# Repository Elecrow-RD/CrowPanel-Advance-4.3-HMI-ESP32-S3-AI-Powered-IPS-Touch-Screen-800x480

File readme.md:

## Menu
### 1, Product picture
### 2, Product version number
### 3, product information
### 4, Use the driver module
### 5,Quick Start
### 6,Folder structure.
### 7,Pin definition
### 8,Guidelines for downloading some of the files from the github repository

### 1, Product picture

### 2, Product version number

|      | Hardware | Software | Remark |
| ---- | -------- | -------- | ------ |
| 1    | V1.0     | V1.0     | old |
| 2    | V1.1     | V1.1     | old |
| 3    | V1.2     | V1.2     | old |
| 4    | V1.3     | V1.2     | latest |

### Version update points:
① Version 1.1 updated the control of backlight on the basis of the original, the backlight of version 1.2 is controlled by STC8H1K28 microcontroller, and the backlight is lit in the program by sending the value to this microcontroller address (0x30). The values are 0-245, where 245 switches off the backlight and 0 is the maximum brightness.

② Version 1.1 has a new option for function switching, see above for details. When using the case, please select the corresponding program to test or modify according to the version number of your motherboard.

## Version 1.2
Only the button component has been updated. All other hardware and I/O pins remain the same as in the previous version.

## Version 1.3
Version 1.3 is simply an update to the previous version that modifies the packaging of the touchscreen FPC connector. There are no other differences.

### 3, product information

| Main Chip-ESP32-S3-WROOM-1-N16R8         |                                                              |
| -------------------------------------------- | ------------------------------------------------------------ |
| CPU/SoC                                      | high-performance Xtensa 32-bit LX7 dual-core processor, with up to 240MHz |
| System Memory                                | 512KB SRAM、8M PSRAM                                         |
| Memory                                       | 16M Flash，384KB ROM                                         |
| Development Language                         | MicroPython、C/C++                                           |
| Development Environment                      | ESP-IDF、Arduino IDE、PlatformIO、MicroPython         |
| **Screen**                                   |                                                              |
| Size                                         | 4.3 inch                                                     |
| Diver IC                                     | ST7265                                                       |
| Resolution                                   | 800*480                                                      |
| Display Panel                                | IPS Panel                                                    |
| Touch Panel                                  | Capacitive Single Touch                                      |
| Viewing Angle                                | 178°                                                         |
| Brightness                                   | 400 cd/m²(Typ.)                                              |
| Color Depth                                  | 16-bit                                                       |
| **Wireless Communication - Onboard Antenna** |                                                              |
| WiFi                                         | Support 2.4GHz, 802.11a/b/g/n                                |
| Bluetooth                                    | Support Bluetooth 5.0 and BLE                                |
| Other                                        | **LoRa**                                                     |
| **Interface/Function**                       |                                                              |
| Interface                                    | USB port, UART, I2C, SD card slot, battery socket, speaker port, microphone, etc. |
| Function                                     | RTC clock, audio amplifier, volume control, battery charge management, USB to UART, etc. |
| **Button/LED Indicator**                     |                                                              |
| Reset Button                                 | Yes, press to reset the device                               |
| Boot Button                                  | Yes, press and hold the power button to burn the program     |
| PWR                                          | Power indicator                                              |
| CHG                                          | Lithium battery charging status, completion indication       |
| **Other**                                    |                                                              |
| Installation method                          | Back hanging, fixed hole                                     |
| Operating temperature                        | -20~70 °C                                                    |
| Storage temperature                          | -30~80 °C                                                    |
| Power Input                                  | 5V/2A, USB or UART terminal                                  |
| Active Area                                  | 95.5mm*54mm                                                  |
| Dimensions                                   | 121.9*75.6*15.3mm                                            |

### 4, Use the driver module

| Name   | dependency library                      |
| ------ | --------------------------------------- |
| LVGL   | lvgl/lvgl@8.3.3                         |
| ST7789 | Adafruit GFX Library<br/>version=1.11.0 |

### 5,Quick Start
### Arduino IDE starts

#### Teaching Case Path：./example/example_code4.3

1.Download the library files used by this product to the 'libraries' folder.

C:\Users\Documents\Arduino\libraries\

2.Open the Arduino IDE

3.Open the code configuration environment and burn it

### ESP-IDF starts

#### Teaching Case Path：./example/idf_code

1.Right-click on an empty space in the project folder and select "Open with VS Code" to open the project.

2.In the IDF plug-in, select the port, then compile and flash

### 6,Folder structure.
|--3D file： Contains 3D model files (.stp) for the hardware. These files can be used for visualization, enclosure design, or integration into CAD software.

|--Datasheet: Includes datasheets for components used in the project, providing detailed specifications, electrical characteristics, and pin configurations.

|--Eagle_SCH&PCB: Contains Eagle CAD schematic (.sch) and PCB layout (.brd) files. These are used for circuit design and PCB manufacturing.

|--example: Provides example code and projects to demonstrate how to use the hardware and libraries. These examples help users get started quickly.

|--factory_firmware: Stores pre-compiled factory firmware that can be directly flashed onto the device. This ensures the device runs the default functionality.

|--factory_sourcecode: Contains the source code for the factory firmware, allowing users to modify and rebuild the firmware as needed.

|--libraries: Includes necessary libraries required for compiling and running the project. These libraries provide drivers and additional functionalities for the hardware.

|--Squareline_studio Instructions for use: Squareline_studio instructions: Demonstrate the use of squareline studio.

### 7,Pin definition

#define HSPI_MISO  4

#define HSPI_MOSI  6

#define HSPI_SCLK  5

#define HSPI_SS    19

#define SD_MOSI 6

#define SD_MISO 4

#define SD_SCK 5

#define SD_CS 0 //The chip selector pin is not connected to IO

#define I2S_DOUT 4

#define I2S_BCLK 5

#define I2S_LRC 6

​      cfg.pin_d0 = GPIO_NUM_21;    // B0

​      cfg.pin_d1 = GPIO_NUM_47;    // B1

​      cfg.pin_d2 = GPIO_NUM_48;   // B2

​      cfg.pin_d3 = GPIO_NUM_45;    // B3

​      cfg.pin_d4 = GPIO_NUM_38;    // B4

​      cfg.pin_d5 = GPIO_NUM_9;    // G0

​      cfg.pin_d6 = GPIO_NUM_10;    // G1

​      cfg.pin_d7 = GPIO_NUM_11;    // G2

​      cfg.pin_d8 = GPIO_NUM_12;   // G3

​      cfg.pin_d9 = GPIO_NUM_13;   // G4

​      cfg.pin_d10 = GPIO_NUM_14;   // G5

​      cfg.pin_d11 = GPIO_NUM_7;  // R0

​      cfg.pin_d12 = GPIO_NUM_17;  // R1

​      cfg.pin_d13 = GPIO_NUM_18;  // R2

​      cfg.pin_d14 = GPIO_NUM_3;  // R3

​      cfg.pin_d15 = GPIO_NUM_46;  // R4

      cfg.pin_henable = GPIO_NUM_42;
      
      cfg.pin_vsync = GPIO_NUM_41;
      
      cfg.pin_hsync = GPIO_NUM_40;
      
      cfg.pin_pclk = GPIO_NUM_39;

#define TOUCH_GT911_SCL 16

#define TOUCH_GT911_SDA 15

### 8,Guidelines for downloading some of the files from the github repository

##### 1, open the link in your browser: https://downgit.github.io/

##### 2, paste the URL of the GitHub destination folder in the input box (example format: `https://github.com/username/repository name/tree/branch name/folder path`)

##### 3, even a that way to download the file.

①Click the “Create Download Link” button to create a download link, copy the link and open it with your browser to download the contents of the corresponding folder directly.

②Click Download, and you can also download it directly.

#### Note: DownGit downloads are stored by default in **your browser's default downloads folder**, usually:

- **Windows**: `C:\Users\your username\Downloads\` (downloads folder)
- **macOS**: `~/Downloads/` (downloads folder)
- **Linux**: `~/Downloads/` (Downloads folder)

If you change the default download path in your browser, the file will be stored in the download location you set. You can find the downloaded file path in your browser's **Download History** (shortcut `Ctrl + J` or `Cmd + J`).

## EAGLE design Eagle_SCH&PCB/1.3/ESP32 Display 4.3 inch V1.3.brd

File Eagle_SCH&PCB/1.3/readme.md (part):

# 4.3-inch CrowPanel Advance HMI Product Hardware Driver Guide

| Item | Details |
|---|---|
| Document Version | V1.0 |
| Date | 2026-07-30 |
| Author | Codex (compiled from the project schematics and verified example code) |
| Applicable Hardware | ESP32 Display 4.3 inch V1.3 / ESP32-S3-N16R8 |
| Schematic Baseline | `1.3/ESP32 Display 4.3 inch V1.3.sch`, `1.3/ESP32-Display-4.3-inch-V1.3.pdf` |
| Software Baseline | Arduino-ESP32 3.3.8; LovyanGFX 1.2.25; LVGL 9.1.0 |

> **Authority rule:** This document uses the actual configurations from successfully tested examples in the repository as the driver baseline and verifies electrical connections against the Eagle V1.3 schematic netlist. If the two conflict, the code values take precedence, and the discrepancy is recorded under “Differences and Risks.” Capabilities without supporting code evidence are marked as “schematic-confirmed/requires hardware verification” and must not be considered verified.

## 1. Summary of Conclusions

- The main controller is an ESP32-S3-WROOM-1-N16R8 (16 MB Flash, 8 MB PSRAM), and the Arduino examples use ESP32 core 3.3.8.
- The display has an 800×480 resolution, RGB565 pixel format, and a 16-bit parallel RGB interface. The stable code baseline uses a 16 MHz pixel clock; the repository also contains examples using 18 MHz and 21 MHz.
- According to the code, the touch controller is a GT911 with I2C address `0x5D`, SDA/SCL on GPIO15/GPIO16, and a 400 kHz bus speed. The code uses polling rather than interrupts.
- According to the code, the onboard STC8 auxiliary MCU uses I2C address `0x30` and handles board-level control of the backlight, touch recovery, speaker, and other functions. Its firmware protocol is not included; only a few verified commands are available.
- GPIO4/5/6 and GPIO19/20 are multiplexed through CH486F devices and DIP switches. SD, I2S audio, wireless SPI, digital microphone, and UART/Zigbee cannot all be enabled simultaneously without restrictions.
- DHT20, nRF24L01, SX1262, and Zigbee are external example devices connected through expansion ports; they are not onboard devices in the V1.3 schematic.

## 2. Evidence Levels and Porting Principles

| Level | Definition | Usage Principle |
|---|---|---|
| A - Code-verified | A complete initialization and execution path exists in the repository's product examples | Preferred values for porting |
| B - Schematic-confirmed | Explicitly present in the V1.3 schematic but not directly driven by the ESP32 examples | May be used for development, but hardware testing must be added |
| C - External example | Example code has been run with the device connected externally through an expansion port | Valid only when the corresponding module is connected and the DIP switches are set to the appropriate mode |
| D - Inferred | Inferred from device functionality or net relationships, without protocol documentation or actual testing | Must not be presented as a production-ready capability |

When porting, select a GPIO multiplexing scenario before initializing peripherals. Do not simply combine all examples. The display and I2C bus may be treated as persistent infrastructure; functions associated with GPIO4/5/6 and GPIO19/20 must be enabled mutually exclusively according to the product scenario.

## 3. Peripheral Overview

| Category | Device/Interface | Connection and Driver | Status |
|---|---|---|---|
| Main controller | ESP32-S3-WROOM-1-N16R8 | Arduino HAL; Wi-Fi; GPIO Matrix; PSRAM | A |
| Display | 4.3-inch 800×480 IPS | 16-bit RGB565, GPIO3/7/9-14/17/18/21/38/45-48, PCLK 39, DE 42, HSYNC 40, VSYNC 41 | A |
| Touch | GT911 (identified by code) | I2C0, SDA 15, SCL 16, `0x5D`, 400 kHz, polling | A |
| Board-control MCU | STC8H1K28 | Shares I2C 15/16 with the ESP32; accessed at `0x30` by the code | A (incomplete protocol) |
| RTC | PCF8563-compatible device + CR1220 | I2C 15/16, 32.768 kHz crystal | B |
| Storage | MicroSD card socket | SPI: MOSI 6, MISO 4, SCK 5; CS not connected to the main controller | A |
| Audio output | NS4168 + right-channel connector | I2S: DOUT 4, BCLK 5, LRCLK 6; board-control command 248 enables the speaker | A |
| Audio input | LMD3526B261 digital microphone | CLK 19, DATA 20; I2S/PDM characteristics require additional testing against the device documentation | B |
| Wireless expansion | J9/J11/J12 | SPI 4/5/6; control pins 8/19/20/2; 3.3 V/optional 5 V | A/C |
| nRF24L01 | External module | SPI 4/5/6, CSN 19, CE 20 | C |
| SX1262 LoRa | External module | SPI 4/5/6, NSS 8, DIO1 20, RESET 19, BUSY 2 | C |
| Zigbee/UART | External module | UART1 RX 19, TX 20, 115200 8N1 | C |
| Temperature and humidity | External DHT20 | I2C 15/16, address `0x38` | C |
| USB-UART | CH340K + automatic download circuit | USB-C D+/D-; connected to ESP32 UART0, EN, and IO0 | B (programming path implicitly used) |
| Expansion interfaces | J2/J10/J13/J14 | UART0, STC UART, I2C, power | B |
| Power management | TP4059, RY3420, MT9201, MOSFET power gating | USB/external 5 V/Li-ion battery input; 3.3 V and backlight boost | B |
| Actuator | Passive buzzer B2 | Driven by STC P2.7 through an NPN transistor | B |
| Indicators/keys | BOOT, RESET, charging/power LEDs, K1 DIP switch | IO0, EN; status LEDs managed by the STC; K1 selects multiplexed channels | B |

## 4. Authoritative GPIO Assignment Table

| ESP32 GPIO | Actual Usage in Code | Schematic Connection | Driver Characteristics/Notes |
|---:|---|---|---|
| 0 | Virtual CS in SD examples; BOOT | BOOT button, not connected to SD CS | Bootstrapping pin; do not connect an external strong pull-down. The CS parameter used for SD does not represent a physical chip-select signal |
| 1 | Driven low for 120 ms during touch recovery, then changed to input | `TP_INT`, connected to the touch FPC INT pin | **Code-precedence discrepancy**; normally an input/polled during operation and briefly driven low in push-pull mode during recovery |
| 2 | SX1262 BUSY; wireless-port BUSY | J11 pin 5 | Input; used when a LoRa module is connected |
| 3 | RGB R3 | LCD R6 (fourth active red bit of the panel) | RGB peripheral output; related to bootstrapping, so avoid external conflicting levels |
| 4 | SD MISO / nRF24 MISO / SX1262 MISO / I2S DOUT | Multiplexed by U11 to SD, wireless, or the amplifier | Direction varies by mode; concurrent contention is strictly prohibited |
| 5 | SD/wireless SCK / I2S BCLK | Multiplexed by U11 | SPI/I2S clock output; concurrent use is strictly prohibited |
| 6 | SD/wireless MOSI / I2S LRCLK | Multiplexed by U11 | Output; concurrent use is strictly prohibited |
| 7 | RGB R0 (code comment) | LCD R3 | RGB output |
| 8 | SX1262 NSS / wireless CS | J11 pin 6 | SPI chip-select output, idle high |
| 9-14 | RGB G0-G5 (code comments) | LCD G2-G7 | RGB outputs |
| 15 | I2C SDA | Touch, RTC, STC, J11/J13 | Open-drain bidirectional; schematic shows a 4.7 kΩ pull-up to 3.3 V |
| 16 | I2C SCL | Touch, RTC, STC, J11/J13 | Open-drain output; schematic shows a 4.7 kΩ pull-up to 3.3 V |
| 17,18 | RGB R1,R2 (code comments) | LCD R4,R5 | RGB outputs |
| 19 | nRF24 CSN / SX1262 RESET / UART1 RX / MIC CLK | Multiplexed by U9; J12 pin 1 | Direction varies by mode; some code only sets it to OUTPUT without writing a level |
| 20 | nRF24 CE / SX1262 DIO1 / UART1 TX / MIC DATA | Multiplexed by U9; J12 pin 2 | Direction varies by mode; must match the DIP-switch position |
| 21 | RGB B0 (code comment) | LCD B3 | RGB output |
| 38 | RGB B4 (code comment) | LCD B7 | RGB output |
| 39 | RGB PCLK | LCD CLK, through 0 Ω | Recommended baseline: 16 MHz; repository examples also use 18/21 MHz |
| 40 | RGB HSYNC | LCD HSYNC | Active low |
| 41 | RGB VSYNC | LCD VSYNC | Active low |
| 42 | RGB DE | LCD DE | Data-enable output |
| 45,46 | RGB B3/R4 (code comments) | LCD B6/R7 | Related to bootstrapping; outputs while the display is running |
| 47,48 | RGB B1/B2 (code comments) | LCD B4/B5 | RGB outputs |
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
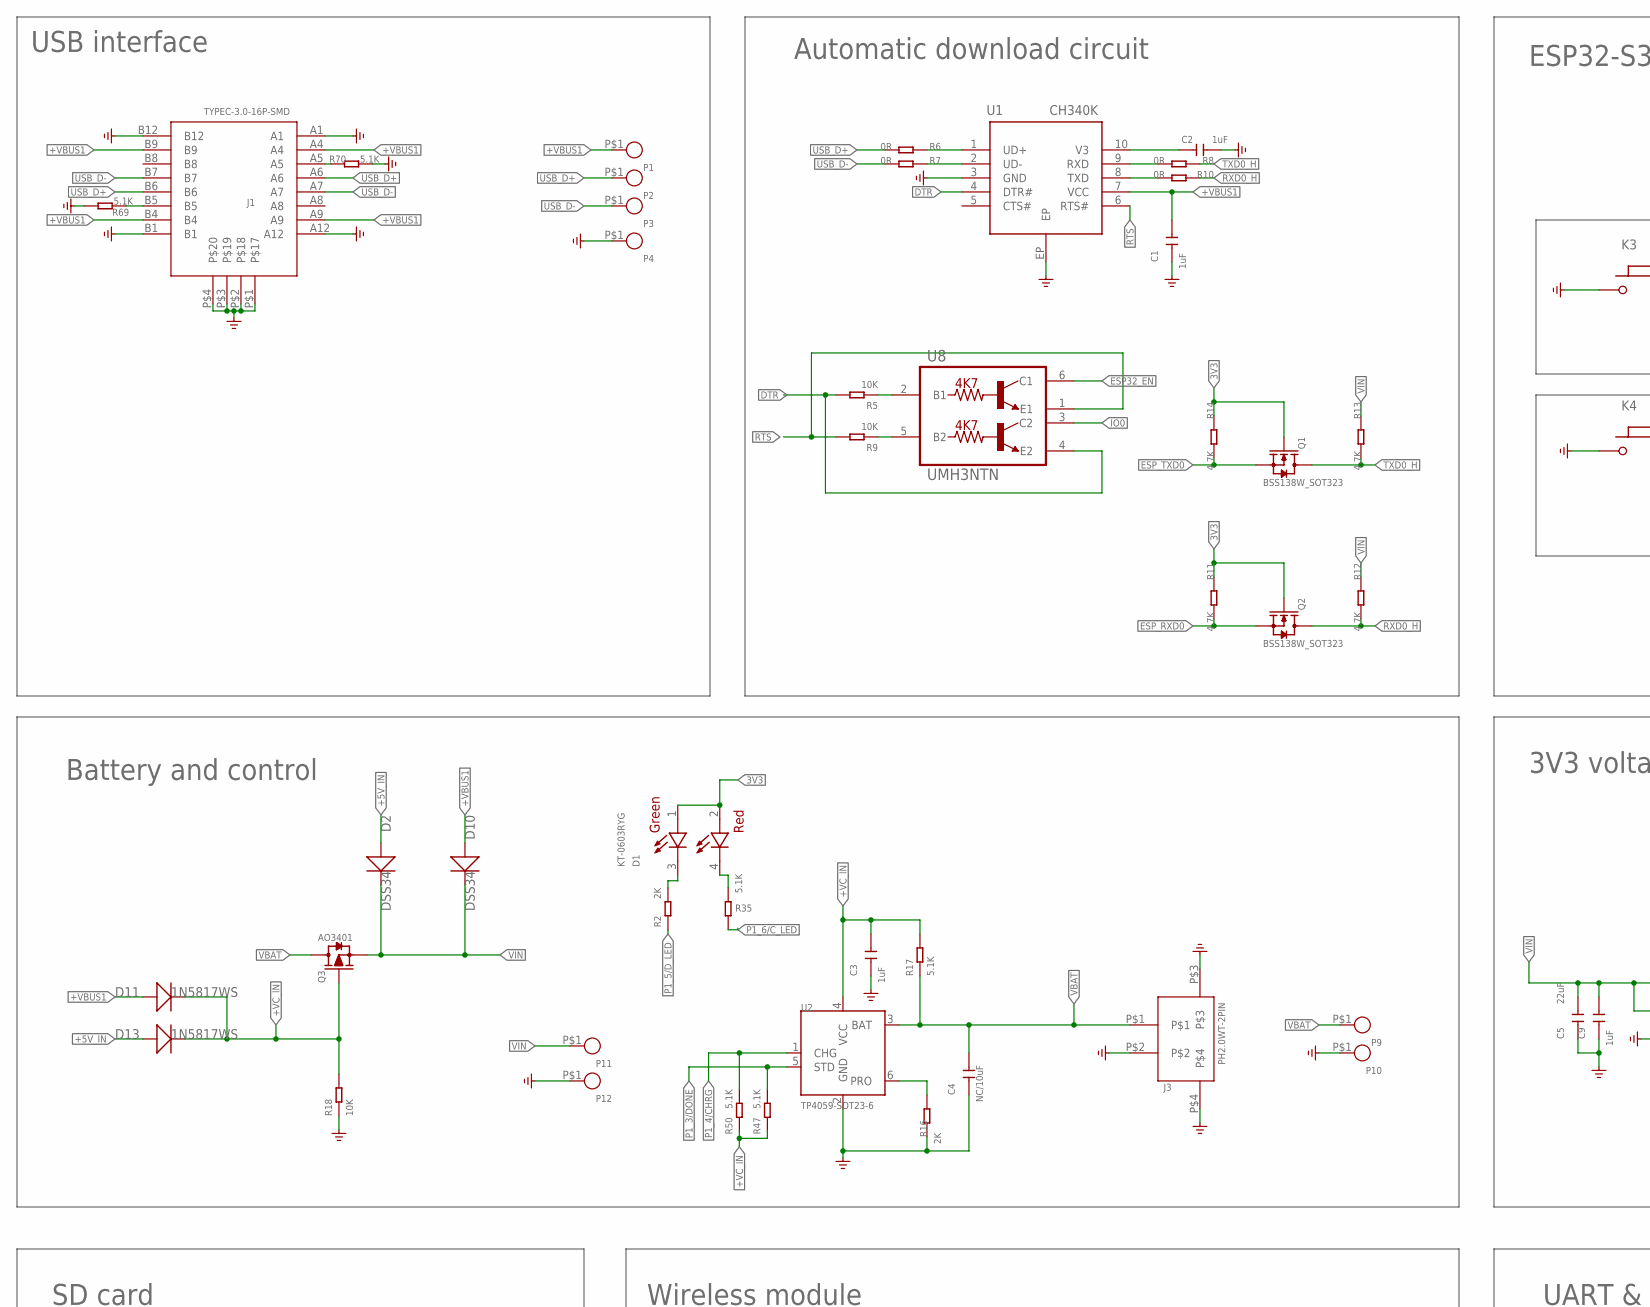
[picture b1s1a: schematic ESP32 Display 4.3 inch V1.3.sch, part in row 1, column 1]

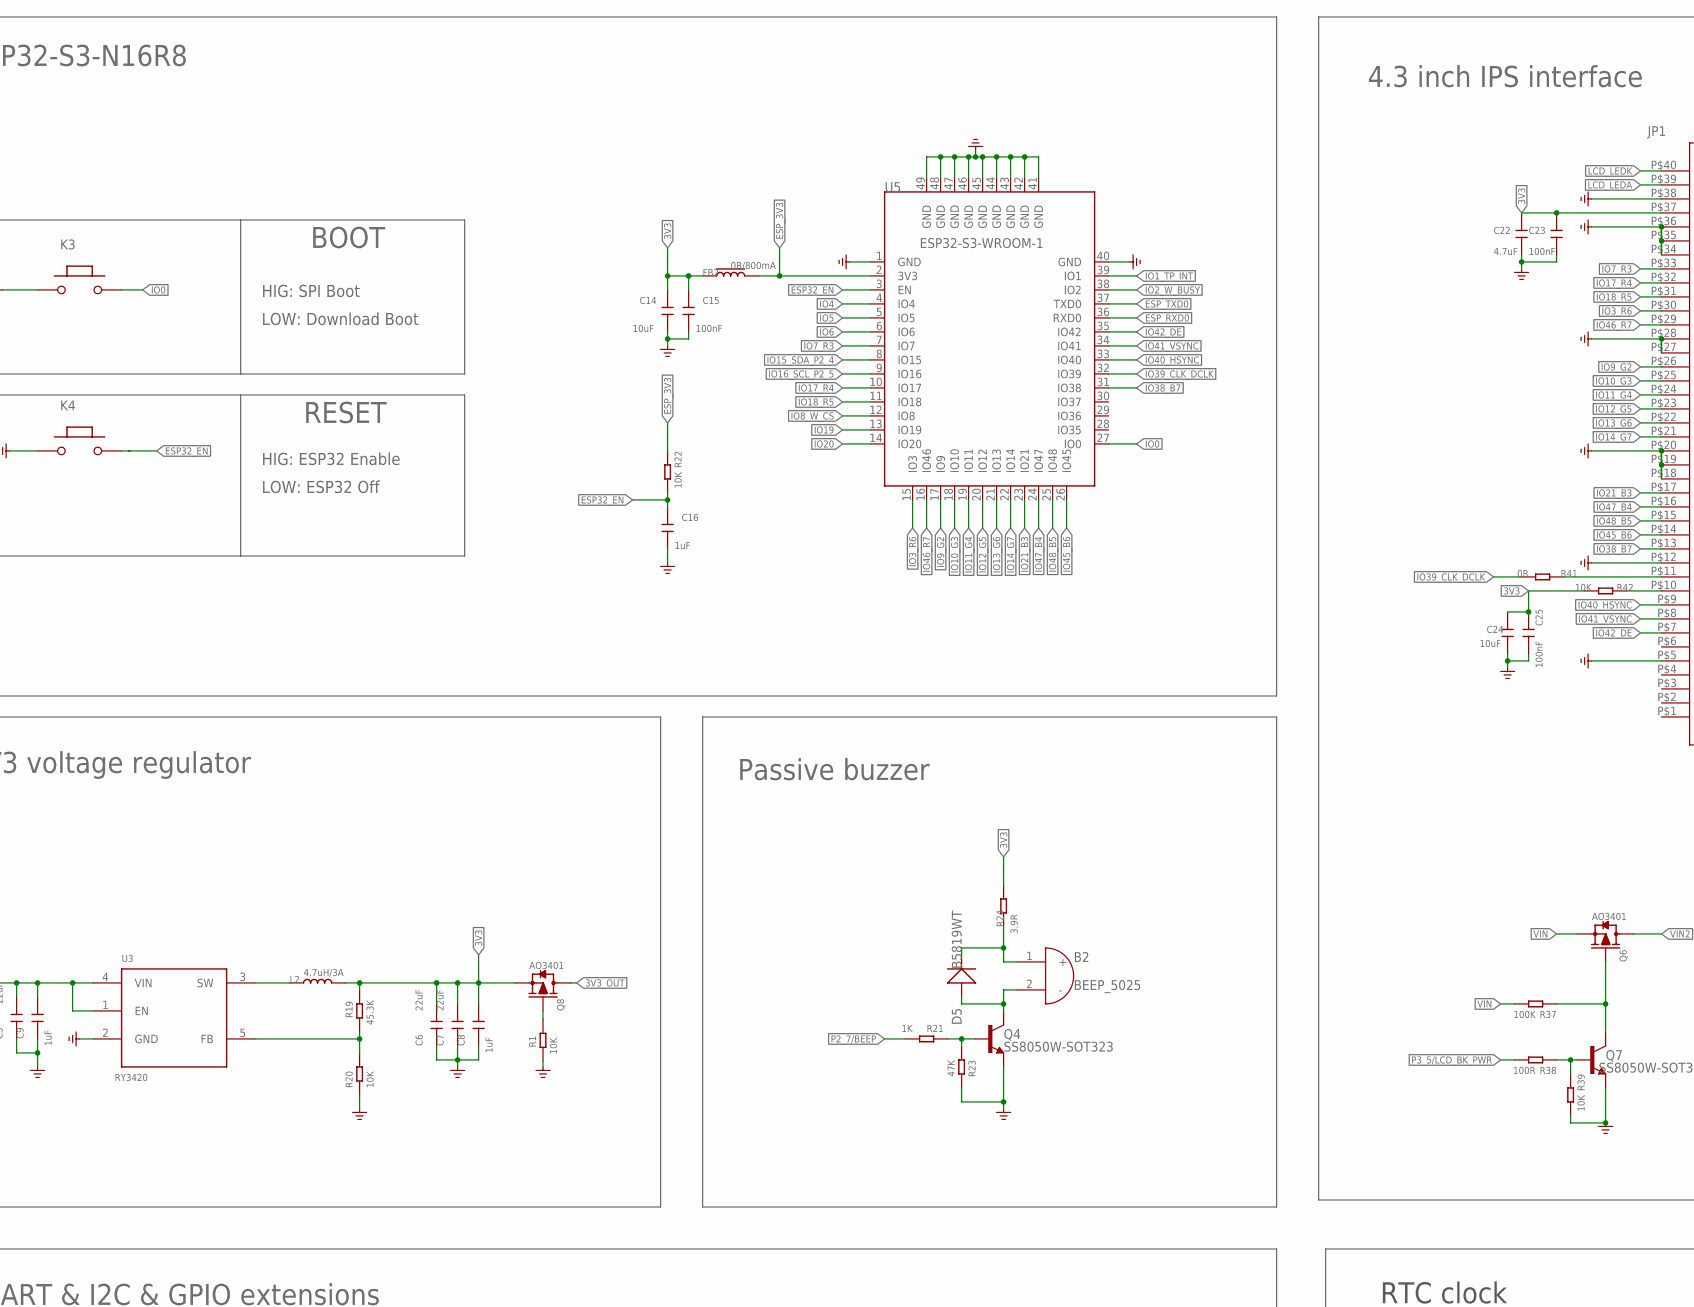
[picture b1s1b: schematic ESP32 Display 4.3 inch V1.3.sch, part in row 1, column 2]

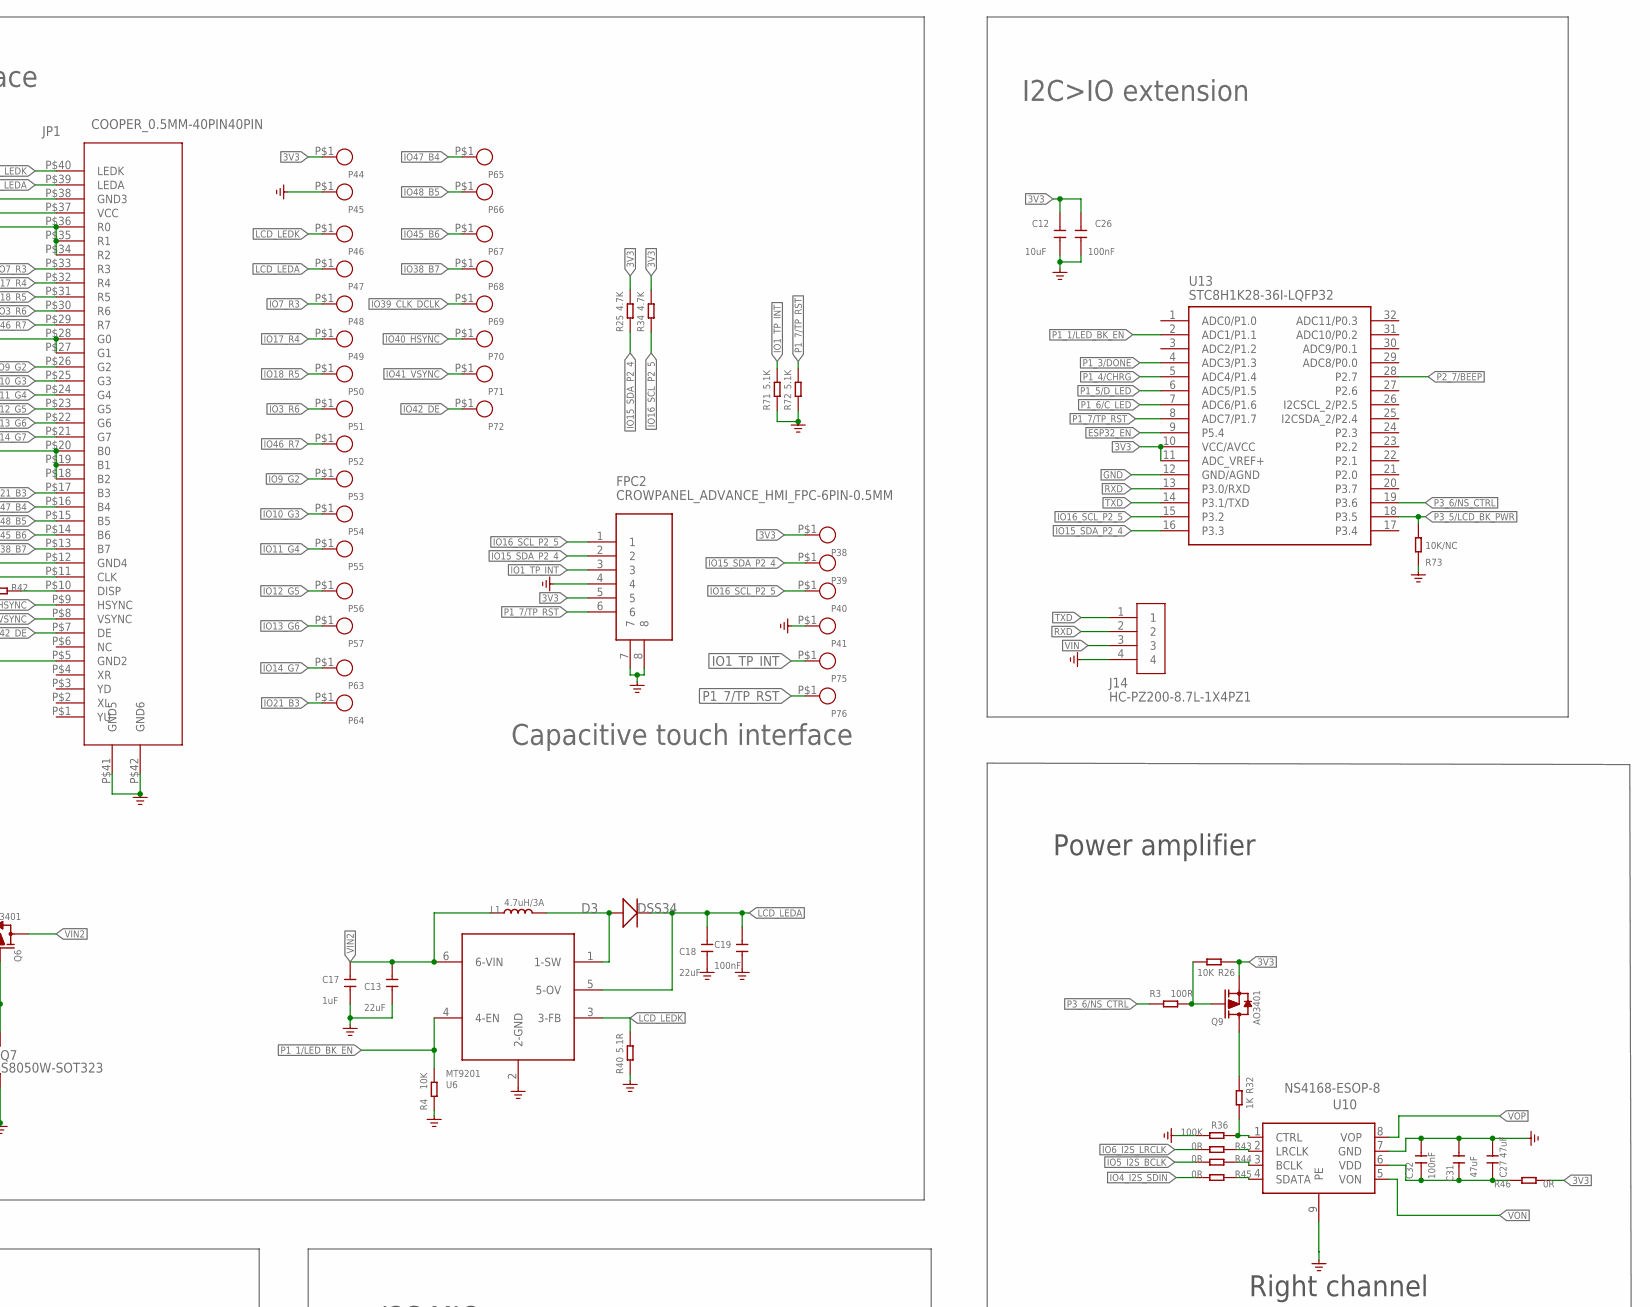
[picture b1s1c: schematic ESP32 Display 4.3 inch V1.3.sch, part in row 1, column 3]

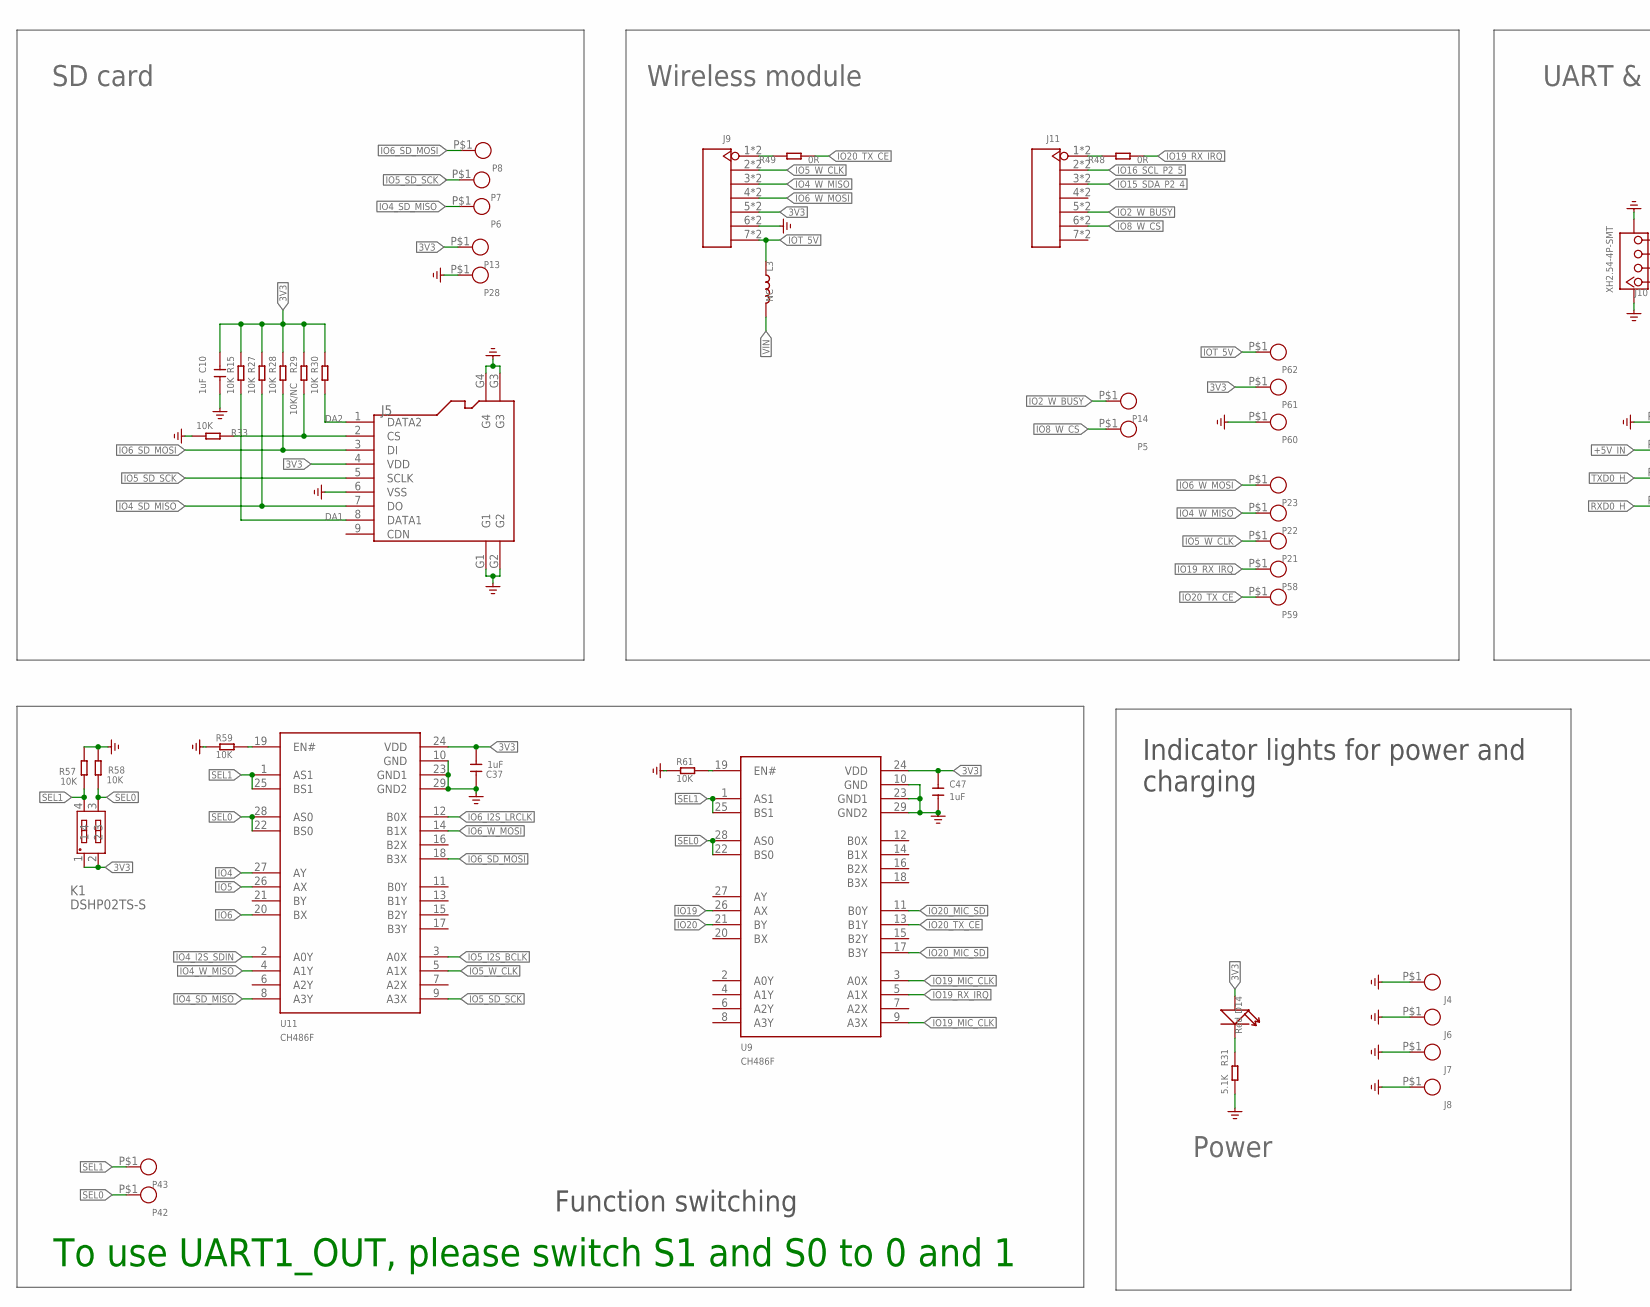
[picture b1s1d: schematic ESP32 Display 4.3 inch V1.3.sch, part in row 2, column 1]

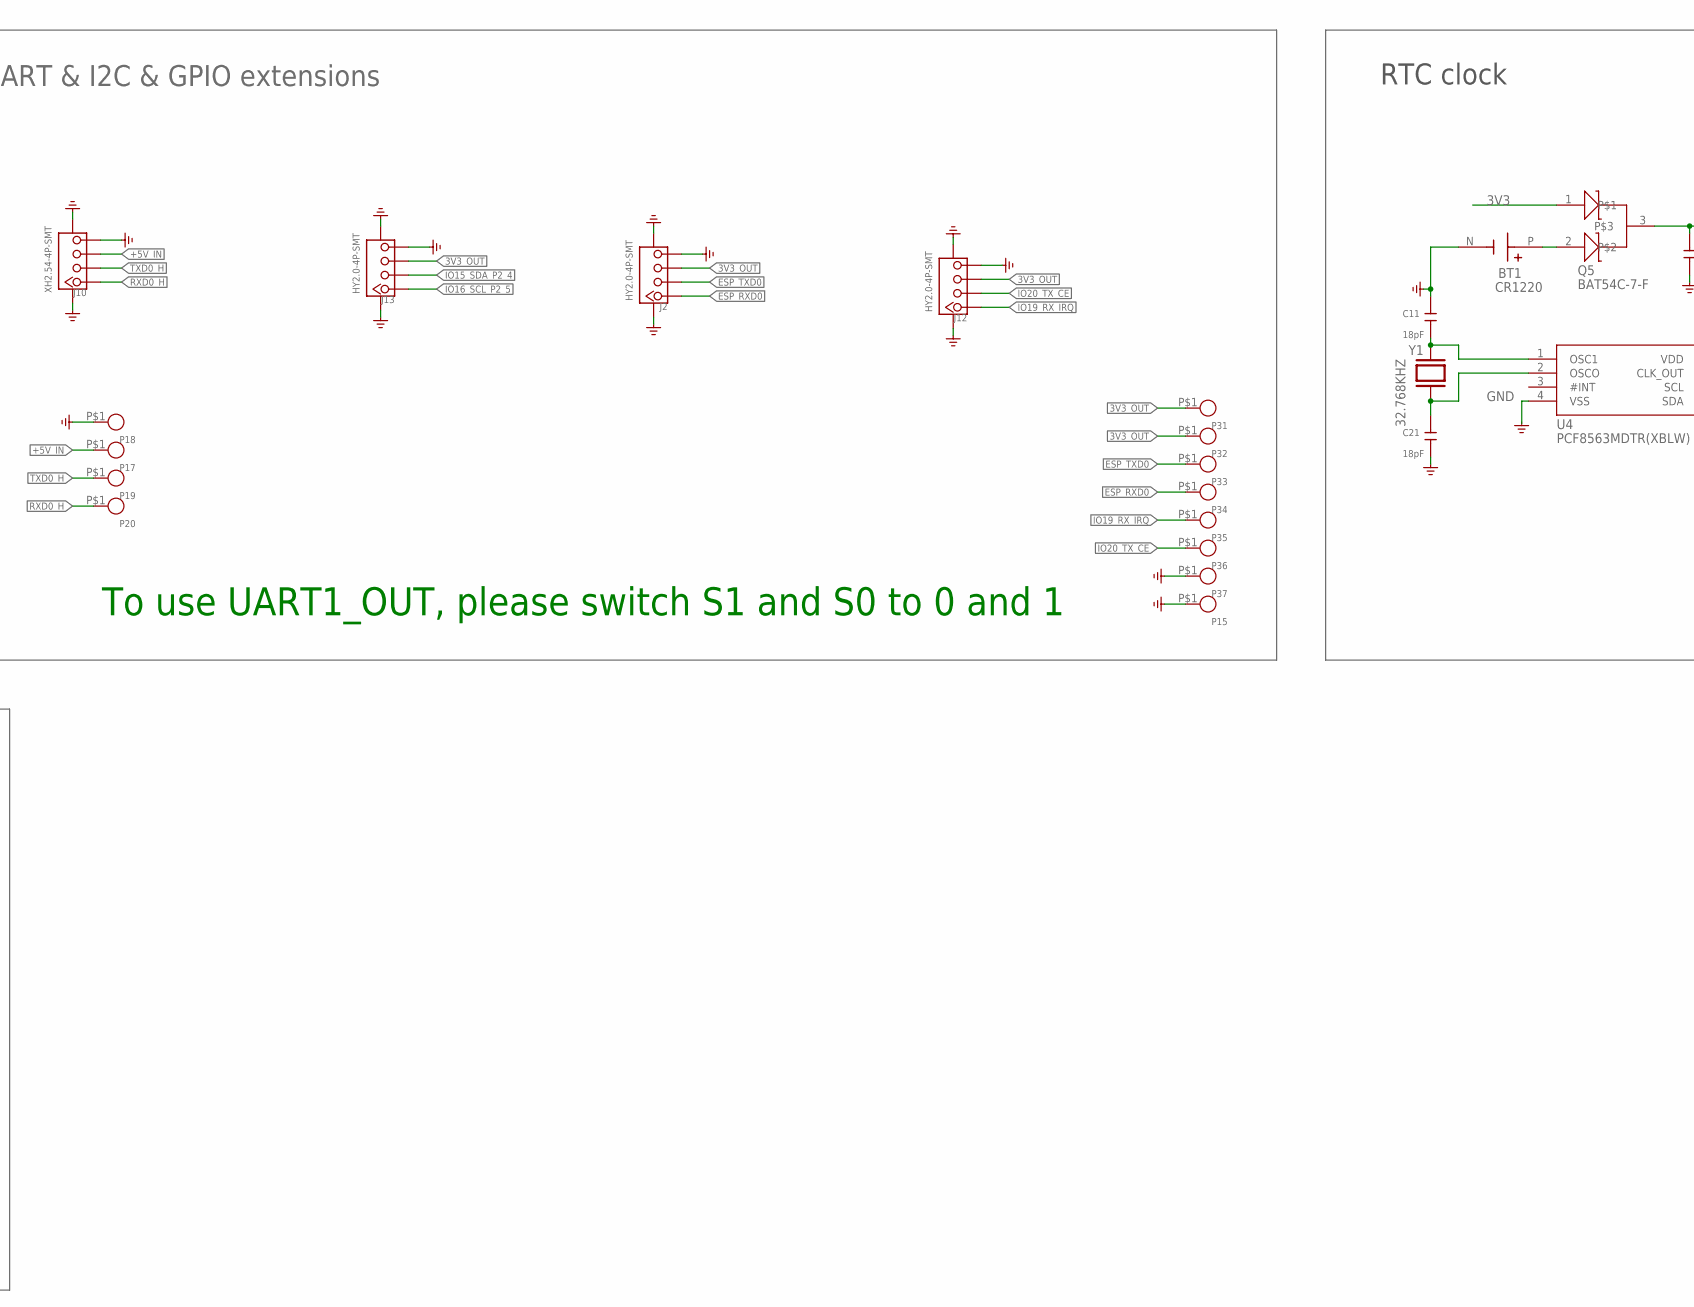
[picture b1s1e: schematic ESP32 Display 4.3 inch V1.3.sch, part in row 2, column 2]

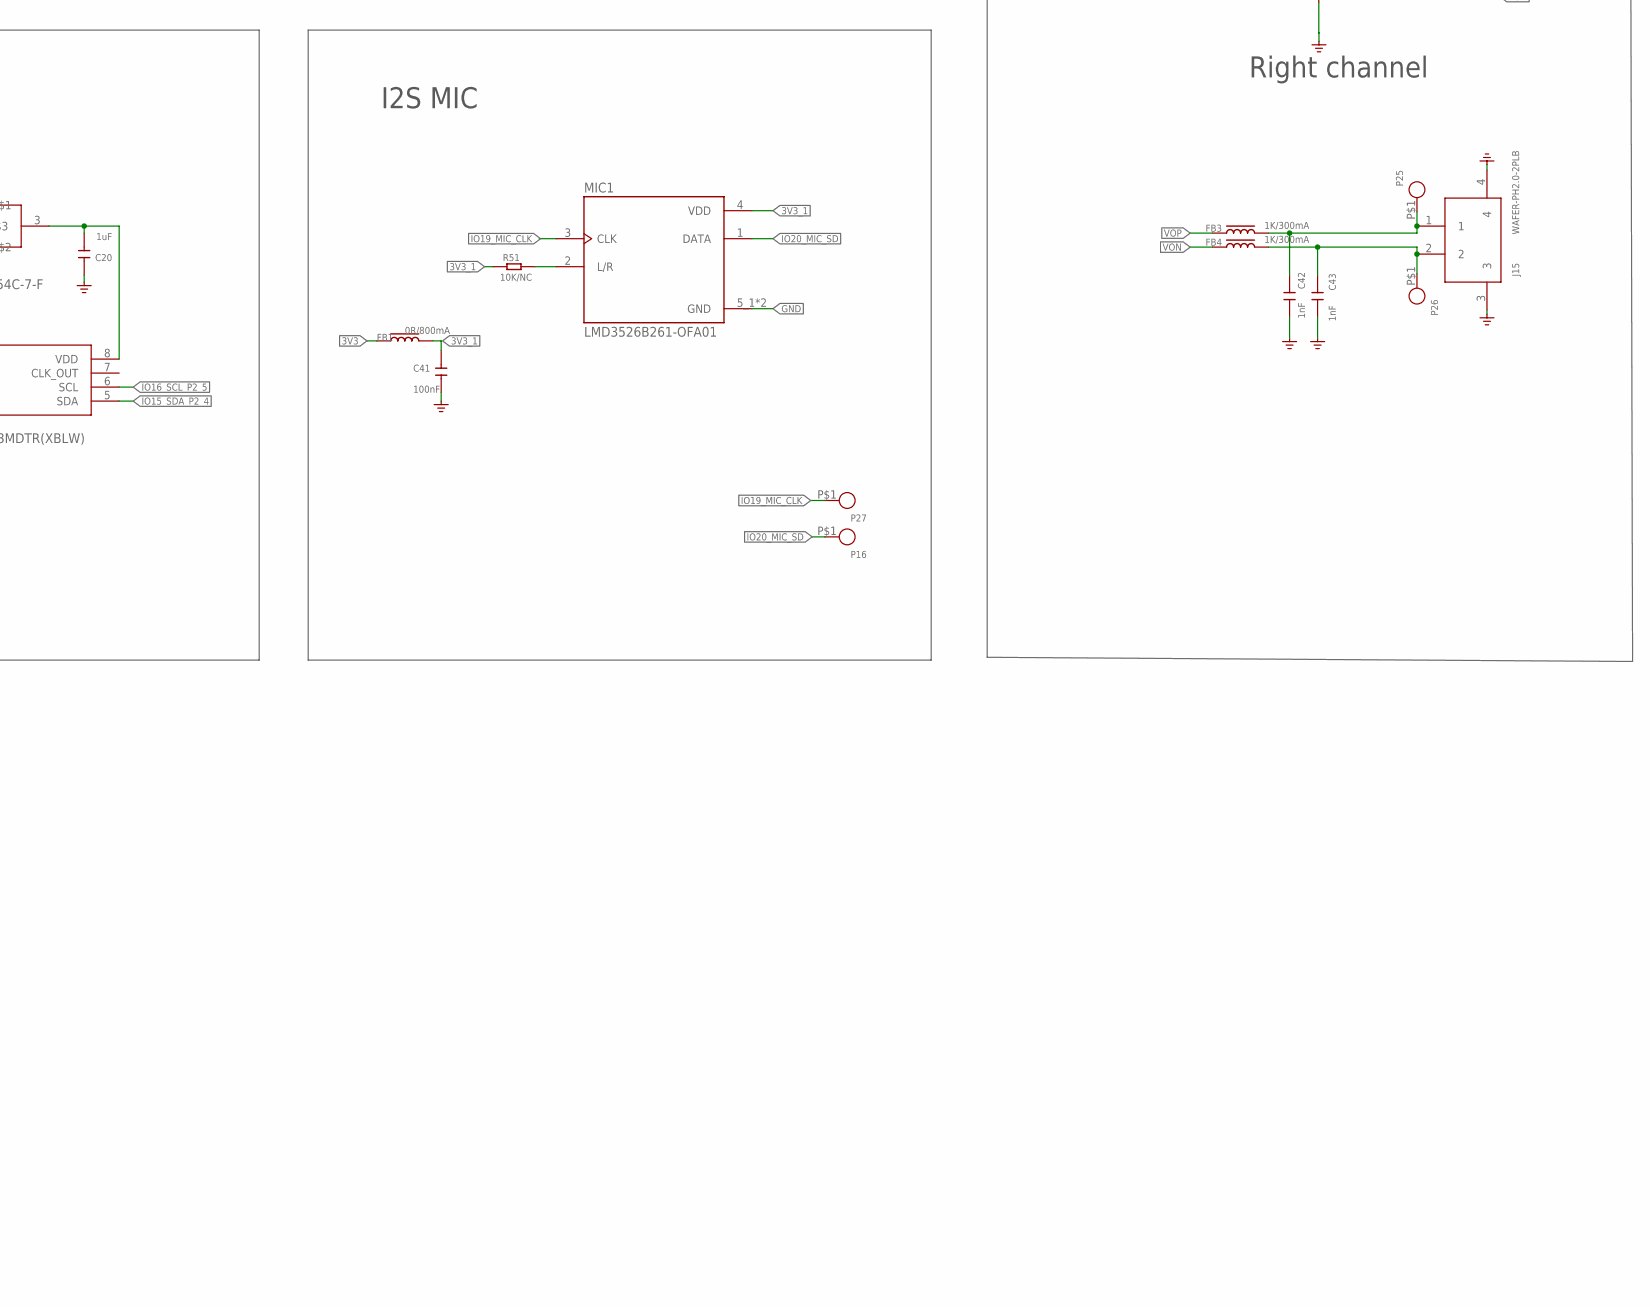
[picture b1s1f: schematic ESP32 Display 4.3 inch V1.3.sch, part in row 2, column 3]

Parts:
B2: BEEP_5025
BT1: CR1220
C1, C2, C3, C8, C9, C10, C16, C17, C20, C37, C47: 1uF; C0603
C4: NC/10uF; C0603
C5, C6, C7, C13, C18: 22uF; C0805
C11, C21: 18pF; C0603
C12, C14, C24: 10uF; C0603
C15, C19, C23, C25, C26, C32, C41: 100nF; C0603
C22: 4.7uF; C0603
C27, C31: 47uF; C0805
C42, C43: 1nF; C0603
D1: KT-0603RYG; LED_KT-0603RYG
D2, D3, D10: DSS34; D_SOD123FL
D5: B5819WT; D_SOD523
D11, D13: 1N5817WS; D_SOD323
D14: Red; LED0603
FB1, FB2: 0R/800mA; L0603
FB3, FB4: 1K/300mA; L0603
FPC2: CROWPANEL_ADVANCE_HMI_FPC-6PIN-0.5MM
J1: TYPEC-3.0-16P-SMD; USB-3.0TYPEC-SMD
J2, J12, J13: HY2.0-4P-SMT; CONNECTOR_4P-SMD-2.0
J3: PH2.0WT-2PIN
J4, J6, J7, J8: THO-M3.25MM-HOLE; THO-M3.2*5MM-HOLE
J5: HOLDER-MICROSD-9P; 9P-SMD-W/-RING
J9, J11: HEADER-7P-18.28X2.5; H7-2.54-18.28X2.5X5MM
J10: XH2.54-4P-SMT; XH2.54-4P-SMD
J14: HC-PZ200-8.7L-1X4PZ1; TEST-PIN-4-2.0MM
J15: WAFER-PH2.0-2PLB; CONN-TH_2P-P2.00_XUNPU_WAFER-PH2.0-2PLB
JP1: COOPER_0.5MM-40PIN40PIN; COOPER_0.5MM*40P
K1: DSHP02TS-S; SW-SMD_DSHP02TS-S_1
K3, K4: BUTTON; 157SW
L1, L2: 4.7uH/3A; L0420
L3: NC; L0603
MIC1: LMD3526B261-OFA01; MIC-SMD_5P-L3.5-W2.7-P1.67
P1, P2, P3, P4, P5, P6, P7, P8, P9, P10, P11, P12, P13, P14, P15, P16, P17, P18, P19, P20, P21, P22, P23, P25, P26, P27, P28, P31, P32, P33, P34, P35, P36, P37, P38, P39, P40, P41, P42, P43, P44, P45, P46, P47, P48, P49, P50, P51, P52, P53, P54, P55, P56, P57, P58, P59, P60, P61, P62, P63, P64, P65, P66, P67, P68, P69, P70, P71, P72, P75, P76: TEST_PADPAD-1.5MM; TEST_PAD-1.5MM
Q1, Q2: BSS138W_SOT323; MOS_SOT323
Q3, Q6, Q8, Q9: AO3401; PMOS_SOT23
Q4, Q7: SS8050W-SOT323; MOS_SOT323
Q5: BAT54C-7-F; SOT-23
R1, R4, R5, R9, R15, R18, R20, R22, R26, R27, R28, R30, R33, R39, R42, R57, R58, R59, R61: 10K; R0603-SP
R2, R16: 2K; R0603-SP
R3, R38: 100R; R0603-SP
R6, R7, R8, R10, R41, R43, R44, R45, R46, R48, R49: 0R; R0603-SP
R11, R12, R13, R14, R25, R34: 4.7K; R0603-SP
R17, R31, R35, R47, R50, R69, R70, R71, R72: 5.1K; R0603-SP
R19: 45.3K; R0603-SP
R21, R32: 1K; R0603-SP
R23: 47K; R0603-SP
R24: 3.9R; R0603-SP
R29, R51, R73: 10K/NC; R0603-SP
R36, R37: 100K; R0603-SP
R40: 5.1R; R0603-SP
U1: CH340K; ESOP-10-EP-150MIL
U2: TP4059-SOT23-6; SOT23-6L
U3: RY3420; IC_SOT23-5
U4: PCF8563MDTR(XBLW); MSOP-8
U5: ESP32-S3-WROOM-1; ESP32-S3-WROOM-1-SMD41
U6: MT9201; COOPER_SOT23-6
U8: UMH3NTN; SOP65P210X100-6N
U9, U11: CH486F; QFN-28_L4.0-W4.0-P0.40-BL-EP2.8
U10: NS4168-ESOP-8
U13: STC8H1K28-36I-LQFP32; QFP80P900X900X165-32N
Y1: 32.768KHZ; SMD3215-2P

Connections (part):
3V3: C6.2, C7.2, C8.2, C10.2, C12.2, C14.2, C15.2, C22.2, C23.2, C24.2, C25.2, C26.2, C37.2, C47.1, D1.1, D1.2, D14.+, FB1.1, FB2.1, FPC2.5, J5.4 (VDD), J9.5, J9.5-5 (5), JP1.P$37 (VCC), K1.1, K1.2, L2.2, P13.P$1, P38.P$1, P44.P$1, P61.P$1, Q1.1 (G), Q2.1 (G), Q5.1, Q8.2 (S), Q9.2 (S), R11.1, R14.1, R15.2, R19.2, R24.2, R25.2, R26.1, R27.2, R28.2, R29.2, R30.2, R34.2, R42.2, R46.2, U9.24 (VDD), U11.24 (VDD), U13.10 (VCC/AVCC), U13.11 (ADC_VREF+)
3V3$: C2.2, U1.10 (V3)
3V3_1: C41.2, FB1.2, MIC1.4 (VDD), R51.2
3V3_NS_CTRL: Q9.3 (D), R32.1
3V3_OUT: J2.3, J12.3, J13.3, P31.P$1, P32.P$1, Q8.3 (D)
+5V_IN: D2.+, D13.+, J10.3, P17.P$1
+VBUS1: C1.2, D10.+, D11.+, J1.A4, J1.A9, J1.B4, J1.B9, P1.P$1, U1.7 (VCC)
+VC_IN: C3.2, D11.-, D13.-, Q3.1 (G), R17.2, R18.2, R47.2, R50.2, U2.4 (VCC)
DA1: J5.8 (DATA1), R15.1
DA2: J5.1 (DATA2), R30.1
DTR: R5.2, U1.4 (DTR#), U8.4 (E2)
ESP32_EN: C16.2, K4.2, R22.2, U5.3 (EN), U8.6 (C1), U13.9 (P5.4)
ESP_3V3: FB2.2, R22.1, U5.2 (3V3)
ESP_RXD0: J2.1, P34.P$1, Q2.2 (S), R11.2, U5.36 (RXD0)
ESP_TXD0: J2.2, P33.P$1, Q1.2 (S), R14.2, U5.37 (TXD0)
GND: BT1.N (-), C1.1, C2.1, C3.1, C4.1, C5.1, C6.1, C7.1, C8.1, C9.1, C10.1, C11.2, C12.1, C13.2, C14.1, C15.1, C16.1, C17.1, C18.2, C19.1, C20.2, C21.1, C22.1, C23.1, C24.1, C25.1, C26.1, C27.2, C31.2, C32.2, C37.1, C41.1, C42.1, C43.1, C47.2, FPC2.4, FPC2.7, FPC2.8, J1.A1, J1.A12, J1.B1, J1.B12, J1.P$1, J1.P$2, J1.P$3, J1.P$4, J2.4, J2.SS1, J2.SS2, J3.P$2, J3.P$3, J3.P$4, J4.P$1, J5.6 (VSS), J5.G1, J5.G2, J5.G3, J5.G4, J6.P$1, J7.P$1, J8.P$1, J9.6, J9.6-6 (6), J10.4, J10.5 (SS1), J10.6 (SS2), J12.4, J12.SS1, J12.SS2, J13.4, J13.SS1, J13.SS2, J14.4, J15.3, J15.4, JP1.P$5 (GND2), JP1.P$12 (GND4), JP1.P$18 (B2), JP1.P$19 (B1), JP1.P$20 (B0), JP1.P$27 (G1), JP1.P$28 (G0)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
IO0: K3.2, U5.27 (IO0), U8.3 (C2)
IO1_TP_INT: FPC2.3, P75.P$1, R71.2, U5.39 (IO1)
IO2_W_BUSY: J11.5, J11.5-5 (5), P14.P$1, U5.38 (IO2)
IO3_R6: JP1.P$30 (R6), P51.P$1, U5.15 (IO3)
IO4: U5.4 (IO4), U11.27 (AY)
IO4_I2S_SDIN: R45.2, U11.2 (A0Y)
IO4_SD_MISO: J5.7 (DO), P6.P$1, R27.1, U11.8 (A3Y)
IO4_W_MISO: J9.3, J9.3-3 (3), P22.P$1, U11.4 (A1Y)
IO5: U5.5 (IO5), U11.26 (AX)
IO5_I2S_BCLK: R44.2, U11.3 (A0X)
IO5_SD_SCK: J5.5 (SCLK), P7.P$1, U11.9 (A3X)
IO5_W_CLK: J9.2, J9.2-2 (2), P21.P$1, U11.5 (A1X)
IO6: U5.6 (IO6), U11.20 (BX)
IO6_I2S_LRCLK: R43.2, U11.12 (B0X)
IO6_SD_MOSI: J5.3 (DI), P8.P$1, R28.1, U11.18 (B3X)
IO6_W_MOSI: J9.4, J9.4-4 (4), P23.P$1, U11.14 (B1X)
IO7_R3: JP1.P$33 (R3), P48.P$1, U5.7 (IO7)
IO8_W_CS: J11.6, J11.6-6 (6), P5.P$1, U5.12 (IO8)
IO9_G2: JP1.P$26 (G2), P53.P$1, U5.17 (IO9)
IO10_G3: JP1.P$25 (G3), P54.P$1, U5.18 (IO10)
IO11_G4: JP1.P$24 (G4), P55.P$1, U5.19 (IO11)
IO12_G5: JP1.P$23 (G5), P56.P$1, U5.20 (IO12)
IO13_G6: JP1.P$22 (G6), P57.P$1, U5.21 (IO13)
IO14_G7: JP1.P$21 (G7), P63.P$1, U5.22 (IO14)
IO15_SDA_P2_4: FPC2.2, J11.3, J11.3-3 (3), J13.2, P39.P$1, R25.1, U4.5 (SDA), U5.8 (IO15), U13.16 (P3.3)
IO16_SCL_P2_5: FPC2.1, J11.2, J11.2-2 (2), J13.1, P40.P$1, R34.1, U4.6 (SCL), U5.9 (IO16), U13.15 (P3.2)
IO17_R4: JP1.P$32 (R4), P49.P$1, U5.10 (IO17)
IO18_R5: JP1.P$31 (R5), P50.P$1, U5.11 (IO18)
IO19: U5.13 (IO19), U9.26 (AX)
IO19_MIC_CLK: MIC1.3 (CLK), P27.P$1, U9.3 (A0X), U9.9 (A3X)
IO19_RX_IRQ: J12.1, P35.P$1, P58.P$1, R48.2, U9.5 (A1X)
IO20: U5.14 (IO20), U9.21 (BY)
IO20_MIC_SD: MIC1.1 (DATA), P16.P$1, U9.11 (B0Y), U9.17 (B3Y)
IO20_TX_CE: J12.2, P36.P$1, P59.P$1, R49.2, U9.13 (B1Y)
IO21_B3: JP1.P$17 (B3), P64.P$1, U5.23 (IO21)
IO38_B7: JP1.P$13 (B7), P68.P$1, U5.31 (IO38)
IO39_CLK_DCLK: P69.P$1, R41.2, U5.32 (IO39)
IO40_HSYNC: JP1.P$9 (HSYNC), P70.P$1, U5.33 (IO40)
IO41_VSYNC: JP1.P$8 (VSYNC), P71.P$1, U5.34 (IO41)
IO42_DE: JP1.P$7 (DE), P72.P$1, U5.35 (IO42)
IO45_B6: JP1.P$14 (B6), P67.P$1, U5.26 (IO45)
IO46_R7: JP1.P$29 (R7), P52.P$1, U5.16 (IO46)
IO47_B4: JP1.P$16 (B4), P65.P$1, U5.24 (IO47)
IO48_B5: JP1.P$15 (B5), P66.P$1, U5.25 (IO48)
IOT_5V: J9.7, J9.7-7 (7), L3.1, P62.P$1
LCD_LEDA: C18.1, C19.2, D3.-, JP1.P$39 (LEDA), P47.P$1, U6.5 (5-OV)
LCD_LEDK: JP1.P$40 (LEDK), P46.P$1, R40.2, U6.3 (3-FB)
unnamed: Q8.1 (G), R1.2
unnamed: D1.3, R2.1
unnamed: D1.4, R35.1
unnamed: D14.-, R31.2
unnamed: R6.1, U1.1 (UD+)
unnamed: R7.1, U1.2 (UD-)
unnamed: R5.1, U8.2 (B1)
unnamed: R9.1, U8.5 (B2)
unnamed: Q9.1 (G), R3.2, R26.2
unnamed: R8.2, U1.9 (RXD)
unnamed: R10.2, U1.8 (TXD)
unnamed: R16.2, U2.6 (PRO)
unnamed: L2.1, U3.3 (SW)
unnamed: R19.1, R20.2, U3.5 (FB)
unnamed: Q4.1 (B), R21.1, R23.1
unnamed: B2.2 (-), D5.+, Q4.3 (C)
unnamed: B2.1 (+), D5.-, R24.1
unnamed: BT1.P (+), Q5.2
unnamed: R32.2, R36.1, U10.1 (CTRL)
unnamed: MIC1.2 (L/R), R51.1
unnamed: D3.+, L1.2, U6.1 (1-SW)
unnamed: J9.1, J9.1-1 (1), R49.1
unnamed: J11.1, J11.1-1 (1), R48.1
unnamed: C20.1, Q5.3, U4.8 (VDD)
unnamed: C21.2, U4.2 (OSCO), Y1.2
unnamed: R43.1, U10.2 (LRCLK)
unnamed: Q6.1 (G), Q7.3 (C), R37.1
unnamed: C11.1, U4.1 (OSC1), Y1.1
unnamed: R44.1, U10.3 (BCLK)
unnamed: Q7.1 (B), R38.1, R39.1
unnamed: R45.1, U10.4 (SDATA)
unnamed: J1.B5, R69.2
unnamed: R61.1, U9.19 (EN#)
unnamed: C27.1, C31.1, C32.1, R46.1, U10.6 (VDD)
unnamed: R59.1, U11.19 (EN#)
unnamed: J1.A5, R70.1
unnamed: JP1.P$11 (CLK), R41.1
unnamed: JP1.P$10 (DISP), R42.1
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
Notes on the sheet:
BOOT
RESET
HIG: SPI Boot
LOW: Download Boot
HIG: ESP32 Enable
LOW: ESP32 Off
Power
USB interface
Automatic download circuit
Battery and control
RTC clock
ESP32-S3-N16R8
4.3 inch IPS interface
Capacitive touch interface
Passive buzzer
3V3 voltage regulator
SD card
Wireless module
UART & I2C & GPIO extensions
Indicator lights for power and charging
I2C>IO extension
I2S MIC
Power amplifier
Right channel
Function switching
To use UART1_OUT, please switch S1 and S0 to 0 and 1
